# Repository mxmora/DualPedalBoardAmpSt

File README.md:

# DualPedalBoardAmpSt
Dual Pedal Board Amp Stereo

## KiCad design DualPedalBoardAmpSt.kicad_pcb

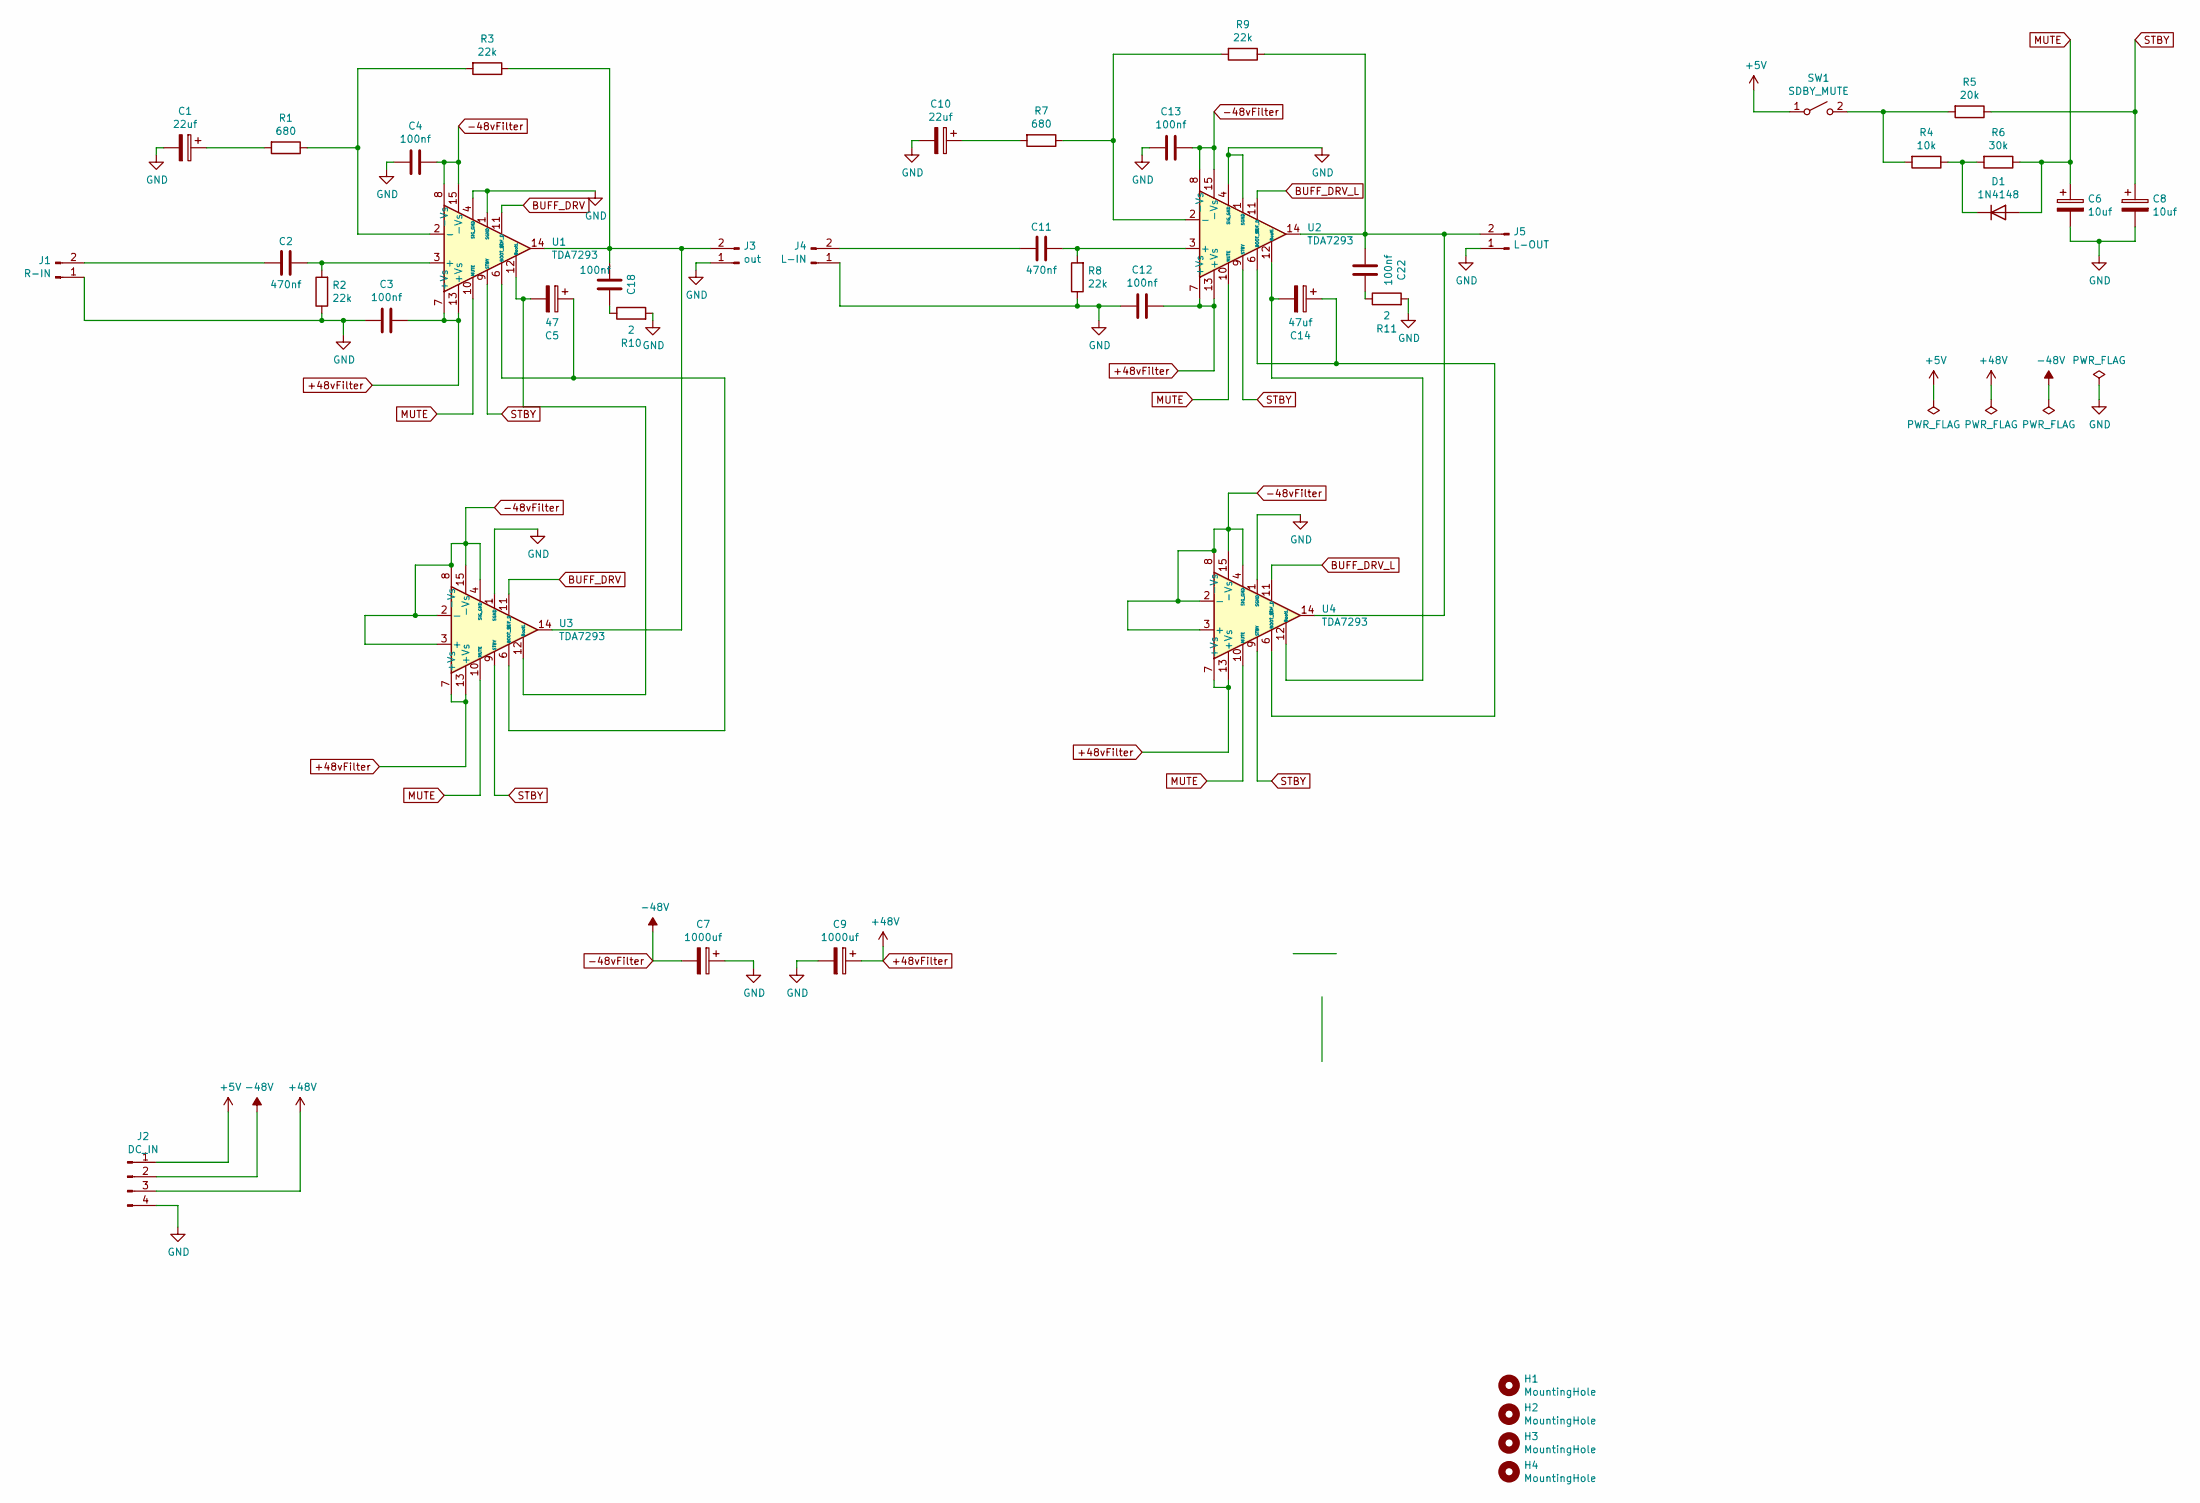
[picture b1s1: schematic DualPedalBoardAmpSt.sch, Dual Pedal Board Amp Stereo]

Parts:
C1, C10: 22uf; CP_Radial_D10.0mm_P5.00mm
C2, C11: 470nf; C_Rect_L7.0mm_W3.5mm_P5.00mm
C3, C4, C12, C13, C18, C22: 100nf; C_Rect_L7.0mm_W3.5mm_P5.00mm
C5: 47; CP_Radial_D10.0mm_P5.00mm
C6, C8: 10uf; CP_Radial_D8.0mm_P3.50mm
C7, C9: 1000uf; CP_Radial_D16.0mm_P7.50mm
C14: 47uf; CP_Radial_D10.0mm_P5.00mm
D1: 1N4148; D_DO-35_SOD27_P7.62mm_Horizontal
H1, H2, H3, H4: MountingHole; MountingHole_3.2mm_M3
J1: R-IN; PinHeader_1x02_P2.54mm_Vertical
J2: DC_IN; TerminalBlock_Phoenix_PT-1,5-4-3.5-H_1x04_P3.50mm_Horizontal
J3: out; PinHeader_1x02_P2.54mm_Vertical
J4: L-IN; PinHeader_1x02_P2.54mm_Vertical
J5: L-OUT; PinHeader_1x02_P2.54mm_Vertical
R1, R7: 680; R_Axial_DIN0207_L6.3mm_D2.5mm_P10.16mm_Horizontal
R2, R3, R8, R9: 22k; R_Axial_DIN0207_L6.3mm_D2.5mm_P10.16mm_Horizontal
R4: 10k; R_Axial_DIN0207_L6.3mm_D2.5mm_P10.16mm_Horizontal
R5: 20k; R_Axial_DIN0207_L6.3mm_D2.5mm_P10.16mm_Horizontal
R6: 30k; R_Axial_DIN0207_L6.3mm_D2.5mm_P10.16mm_Horizontal
R10, R11: 2; R_Axial_DIN0207_L6.3mm_D2.5mm_P10.16mm_Horizontal
SW1: SDBY_MUTE; PinHeader_1x02_P2.54mm_Vertical
U1, U2, U3, U4: TDA7293; TO-220-15_P2.54x2.54mm_StaggerOdd_Lead4.58mm_Vertical

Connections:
+5V: J2.1, SW1.1 (A)
+48vFilter: C3.1, C9.1, C12.1, J2.3, U1.7 (+Vs), U1.13 (+Vs), U2.7 (+Vs), U2.13 (+Vs), U3.7 (+Vs), U3.13 (+Vs), U4.7 (+Vs), U4.13 (+Vs)
-48vFilter: C4.1, C7.2, C13.1, J2.2, U1.8 (-Vs), U1.15 (-Vs), U2.8 (-Vs), U2.15 (-Vs), U3.2 (-), U3.3 (+), U3.4 (SIG_GND), U3.8 (-Vs), U3.15 (-Vs), U4.2 (-), U4.3 (+), U4.4 (SIG_GND), U4.8 (-Vs), U4.15 (-Vs)
BUFF_DRV: U1.11 (BUF_D), U3.11 (BUF_D)
BUFF_DRV_L: U2.11 (BUF_D), U4.11 (BUF_D)
GND: C1.2, C3.2, C4.2, C6.2, C7.1, C8.2, C9.2, C10.2, C12.2, C13.2, J1.1, J2.4, J3.1, J4.1, J5.1, R2.1, R8.1, R10.2, R11.2, U1.1 (SGND), U1.4 (SIG_GND), U2.1 (SGND), U2.4 (SIG_GND), U3.1 (SGND), U4.1 (SGND)
MUTE: C6.1, D1.2 (A), R6.1, U1.10 (MUTE), U2.10 (MUTE), U3.10 (MUTE), U4.10 (MUTE)
unnamed: C1.1, R1.2
unnamed: C2.1, R2.2, U1.3 (+)
unnamed: C2.2, J1.2
unnamed: C5.1, U1.6 (BOOT_ST), U3.6 (BOOT_ST)
unnamed: C5.2, U1.12 (BootL), U3.12 (BootL)
unnamed: C10.1, R7.2
unnamed: C11.1, R8.2, U2.3 (+)
unnamed: C11.2, J4.2
unnamed: C14.1, U2.6 (BOOT_ST), U4.6 (BOOT_ST)
unnamed: C14.2, U2.12 (BootL), U4.12 (BootL)
unnamed: C18.1, R10.1
unnamed: C18.2, J3.2, R3.1, U1.14, U3.14
unnamed: C22.1, R11.1
unnamed: C22.2, J5.2, R9.1, U2.14, U4.14
unnamed: D1.1 (K), R4.1, R6.2
unnamed: R1.1, R3.2, U1.2 (-)
unnamed: R4.2, R5.2, SW1.2 (B)
unnamed: R7.1, R9.2, U2.2 (-)
STBY: C8.1, R5.1, U1.9 (STBY), U2.9 (STBY), U3.9 (STBY), U4.9 (STBY)

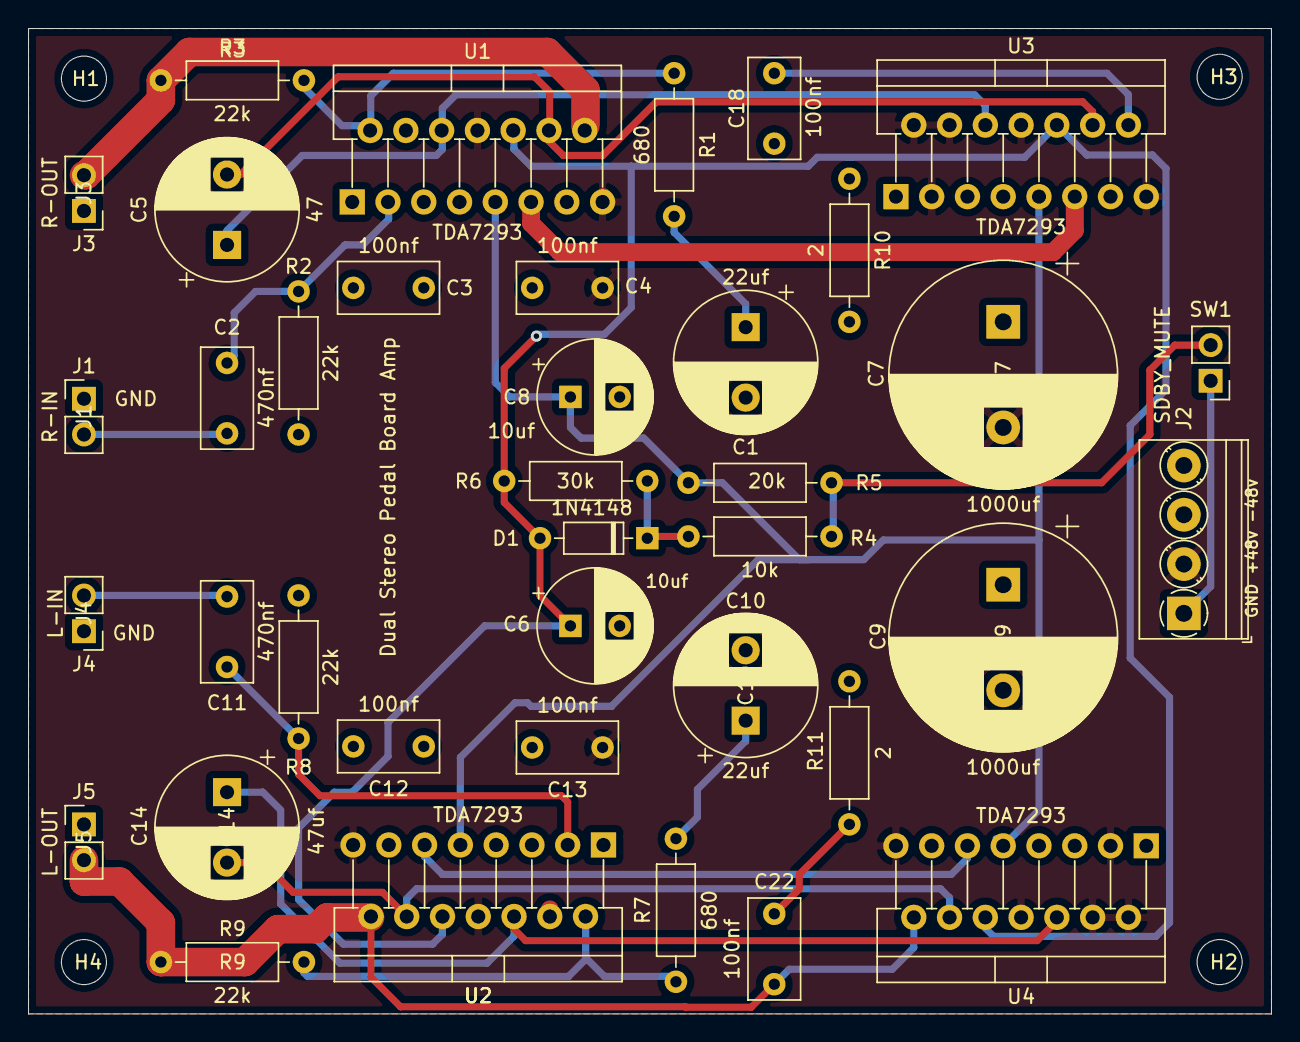
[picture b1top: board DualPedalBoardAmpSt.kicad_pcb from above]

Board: 4 copper layers, 88.3 x 70.0 mm, 42 parts (0 on the bottom side), 26 nets.

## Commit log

2020-12-22 First Checkin
2021-01-05 improve design
